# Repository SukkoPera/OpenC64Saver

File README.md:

## OpenC64Saver

OpenC64Saver is an Open Hardware implementation of the [Computer Saver device developed by Ray Carlsen](https://portcommodore.com/rcarlsen/cbm/c64/SAVER/saver.txt), mainly targeted at Commodore 64 users, but also usable on VIC-20 computers.

### Summary
> This over-voltage protection unit is designed to prevent damage to
the Commodore 64 computer due to a failing power supply. One of the ways
the Commodore "brick" power supply can fail is from a shorted internal
5 volt regulator. That fault puts excessive voltage into the computer
and damages chips such as RAM very quickly... and silently. The Saver
protector is essentially a fast-acting electronic circuit breaker. It
functions to quickly cut off the 5 volt supply line to the computer if
the voltage exceeds about 5.4 volts. It is not a "crowbar" device but
opens the line from the supply to the computer before the voltage gets
high enough to do damage. That's the safest way to do it. After-market
power supplies, even switching types, can fail at any time. Switchers
are more reliable and much less prone to catastrophic failures but can
still cause damage to the computer if they fail. This Saver is designed
to protect any computer that uses the standard Commodore "brick" power
supply as well as any newer switch-mode PS. Computers include all
versions of the C64, the later CR version of the VIC20, and the Plus/4.
Because of its square power connector, an external Saver is possible
for the Plus/4 but its power socket would have to be changed to the
round C64 version because four pin square DIN connectors are not
available. - Ray Carlsen

### Installation

#### Internal
> There are several ways to add this protection device to your system.
One way is to install the components or a completed module inside the
computer. That way, it is protected from any supply plugged into it. If
you have more than one computer, a protector can be installed in each
one. To install the protector circuit inside a C64, it is necessary to
open the +5 volt line on the circuit board. Input and output lines of
the protector are wired to each end of the now-open circuit. If your
C64 board differs from the pictures on my site, you will have to locate
the correct area of your board to open the line and make the connections.
In all internal versions, the correct point is electrically between the
power connector and the power switch. There are at least five board
versions of that computer, each with a different PC board layout, and
the physical connections will be specific for each board.

Ray's C64 motherboard pictures can be found [here](https://portcommodore.com/rcarlsen/cbm/c64/SAVER/MOBOs/).

For the VIC-20 see [this](https://portcommodore.com/rcarlsen/cbm/vic20/VIC20CR/saver%20mod.jpg). Note that you will have to cut a trace.

#### External
You can also put your OpenC64Saver in an external box, by using one of those common small boxes for electronic stuff. If you have a 3D printer available, you can also print [this excellent case by Ruben Coolen](https://www.thingiverse.com/thing:3795541) (Thanks!!!).

The connectors you will need are called *DIN-7* (formally *DIN 45329*) and are very common and easy to find in both cable- and panel-mount versions. Please refer to [this page](https://www.c64-wiki.com/wiki/Power_Supply_Connector) for the wiring.

This way you will be able to use a single OpenC64Saver with different computers, both C64s and VIC-20s.

### Configuration
OpenC64Saver includes a trimmer to set the cut-off voltage:

> Because of fairly wide Saver component tolerances and to
accommodate the normal voltage variations of even good power supplies,
the basic Saver circuit must be "trimmed" so the voltage cuts off at
about 5.4 volts DC. If set too high, it will not protect the computer;
if too low it will trip prematurely even with a good PS. Feedback from
a few users indicated the Saver would trip when they turned their
computer off, and it remained in failsafe mode until unplugged from the
PS. Apparently some power supplies output can jump up past the failsafe
point when the load on them is suddenly removed (computer off). That's
why the trip point is set as high as it is. 5.4 volts is still under
the "absolute maximum rating" specification for the RAM chips.

To properly set the cut-out voltage you will need a variable DC supply and a voltmeter:
- Slowly increase the supply voltage until you hear the relay cut in (voltage appears on the relay output side)
- Continue advancing it until the relay cuts out again. The voltage at that instant is the trip point of the device.
- If it is too high, decrease the supply voltage until the relay cuts in again, rotate the trimmer screw, and repeat the above procedure.

> Note that the Zener diode is somewhat temperature sensitive. If very cold, the
trip point will read high, and if hot from soldering, the trip point will be low. Therefore, the mounting of the Saver components, if inside the computer, should be away from all heat producing components.

### License
OpenC64Saver is Open Hardware. If you make any modifications to the board, please contribute them back.

### Disclaimer
OpenC64Saver is provided to you 'as is' and without any express or implied warranties whatsoever with respect to its functionality, operability or use, including, without limitation, any implied warranties of merchantability, fitness for a particular purpose or infringement. We expressly disclaim any liability whatsoever for any direct, indirect, consequential, incidental or special damages, including, without limitation, lost revenues, lost profits, losses resulting from business interruption or loss of data, regardless of the form of action or legal theory under which the liability may be asserted, even if advised of the possibility or likelihood of such damages.

### Support the Project
Since the project is open you are free to get the PCBs made by your preferred manufacturer, however in case you want to support the development, you can order them from PCBWay through this link:

You get my gratitude and cheap, professionally-made and good quality PCBs, I get some credit that will help with this and [other projects](https://www.pcbway.com/project/member/shareproject/?bmbid=41100). You won't even have to worry about the various PCB options, it's all pre-configured for you!

Also, if you still have to register to that site, [you can use this link](https://www.pcbway.com/setinvite.aspx?inviteid=41100) to get some bonus initial credit (and yield me some more).

Again, if you want to use another manufacturer, feel free to, don't feel obligated :). But then you can buy me a coffee if you want:

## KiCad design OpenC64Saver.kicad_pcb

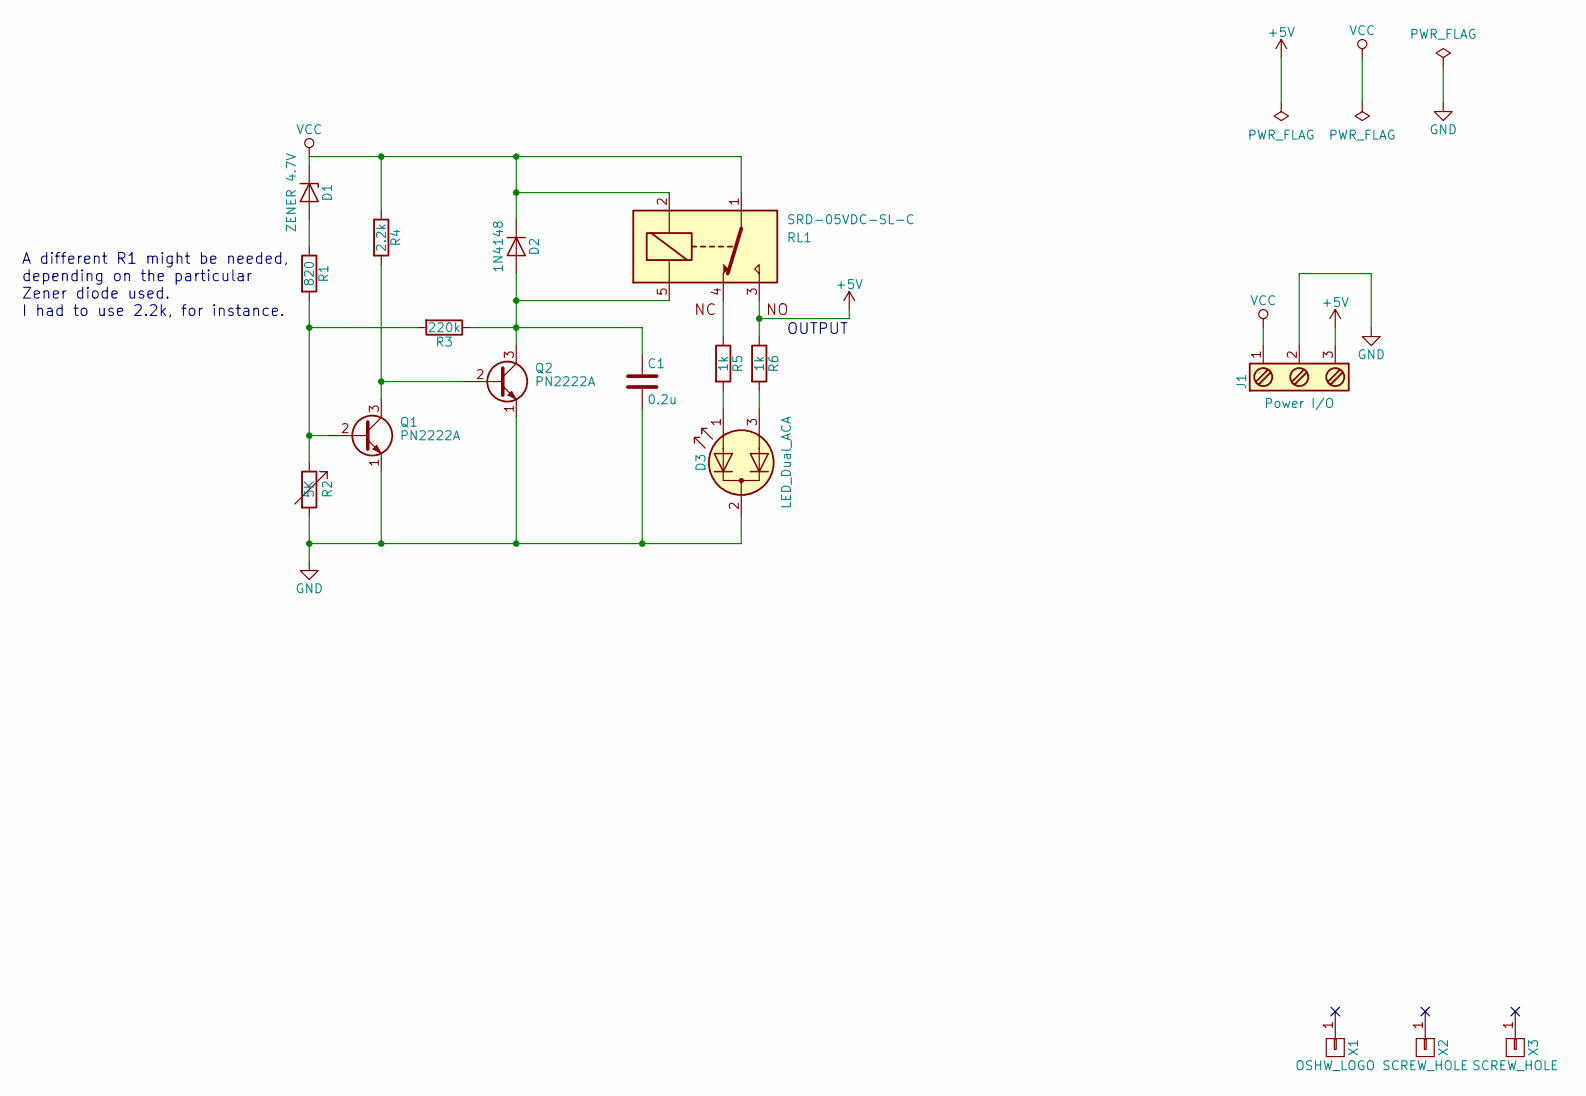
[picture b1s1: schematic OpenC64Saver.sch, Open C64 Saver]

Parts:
C1: 0.2u; C_Disc_D7.0mm_W2.5mm_P5.00mm
D1: ZENER 4.7V; diode_do35
D2: 1N4148; diode_do35
D3: LED_Dual_ACA; Pin_Header_Straight_1x03
J1: Power I/O; mors_3p
Q1, Q2: PN2222A; to92_ebc
R1: 820; R_Axial_DIN0207_L6.3mm_D2.5mm_P10.16mm_Horizontal
R2: 5K; trimmer_vishay_64w
R3: 220k; R_Axial_DIN0207_L6.3mm_D2.5mm_P10.16mm_Horizontal
R4: 2.2k; R_Axial_DIN0207_L6.3mm_D2.5mm_P10.16mm_Horizontal
R5, R6: 1k; R_Axial_DIN0207_L6.3mm_D2.5mm_P10.16mm_Horizontal
RL1: SRD-05VDC-SL-C; Relay_SANYOU_SRD_Series_Form_C
X1: OSHW_LOGO; Logo_copper_OSHW_6x6mm
X2, X3: SCREW_HOLE; 1pin

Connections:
+5V: J1.3, R6.1, RL1.3
GND: C1.2, D3.2 (K), J1.2, Q1.1 (E), Q2.1 (E), R2.2
unnamed: C1.1, D2.2 (A), Q2.3 (C), R3.1, RL1.5
unnamed: D1.2 (A), R1.1
unnamed: D3.1 (A1), R5.2
unnamed: D3.3 (A2), R6.2
unnamed: Q1.2 (B), R1.2, R2.1, R3.2
unnamed: Q1.3 (C), Q2.2 (B), R4.2
unnamed: R5.1, RL1.4
VCC: D1.1 (K), D2.1 (K), J1.1, R4.1, RL1.1, RL1.2

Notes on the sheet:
OUTPUT
A different R1 might be needed, depending on the particular Zener diode used. I had to use 2.2k, for instance.

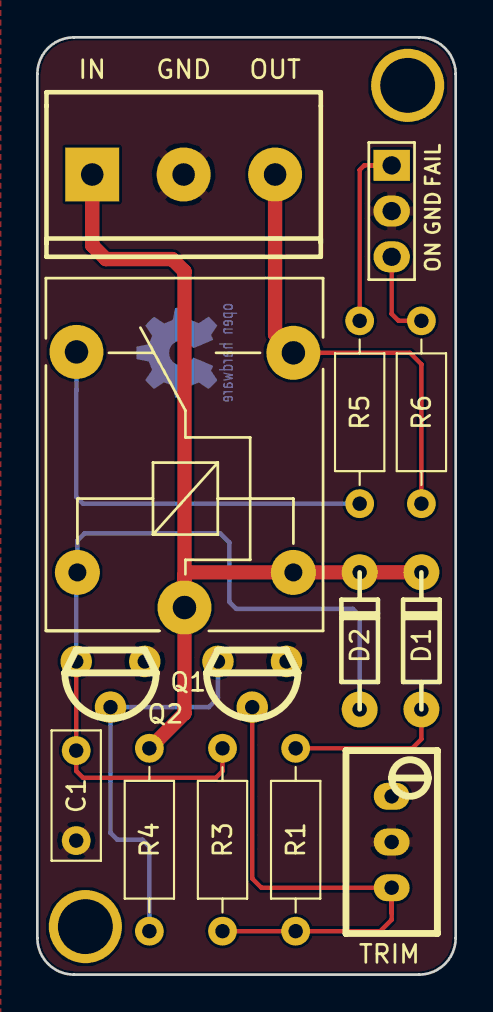
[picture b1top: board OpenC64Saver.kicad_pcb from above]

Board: 2 copper layers, 23.2 x 52.1 mm, 17 parts (1 on the bottom side), 10 nets.

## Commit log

2017-09-02 Initial import
2017-09-02 Relabel some components
2017-09-02 Work in progress
2017-09-02 Rename files to "official" project name
2017-09-02 Full board redesign to make it narrower
2017-09-30 Make board slightly larger so silkscreen doesn't get cut
2017-09-30 Tighter soldermask
2017-09-30 Bump version
2017-09-30 Even tighter soldermask
2017-10-02 Fix 3D models
2017-10-02 Add docs
2017-10-02 Smooth corners
2017-10-07 Move some traces
2017-10-07 Move version number
2017-10-07 Remove R2, decrease R1 (and add note. The variable resistor is usually enough. It was R7, it is now R2.
2017-10-07 Rotate R2 to reorient silkscreen on PCB
2017-10-07 Remove R2 and reorient trimmer (which is now R2)
2017-10-07 Add RELEASES to .gitignore
2017-10-07 Fit a 2nd screw hole
2017-10-08 Fix 3D models and add doc files
2017-10-10 Restore images of last released board
2017-12-30 Update parts for latest Kicad
2018-01-04 Final touches for V3
2018-01-04 Crop images
2018-09-16 Experimental full through-hole version
2018-09-16 Minor fix
2018-09-16 Update PCB purchase link for V4
2019-08-26 Add coffee
2019-08-26 Add info on external version
2023-07-25 Fix #7
